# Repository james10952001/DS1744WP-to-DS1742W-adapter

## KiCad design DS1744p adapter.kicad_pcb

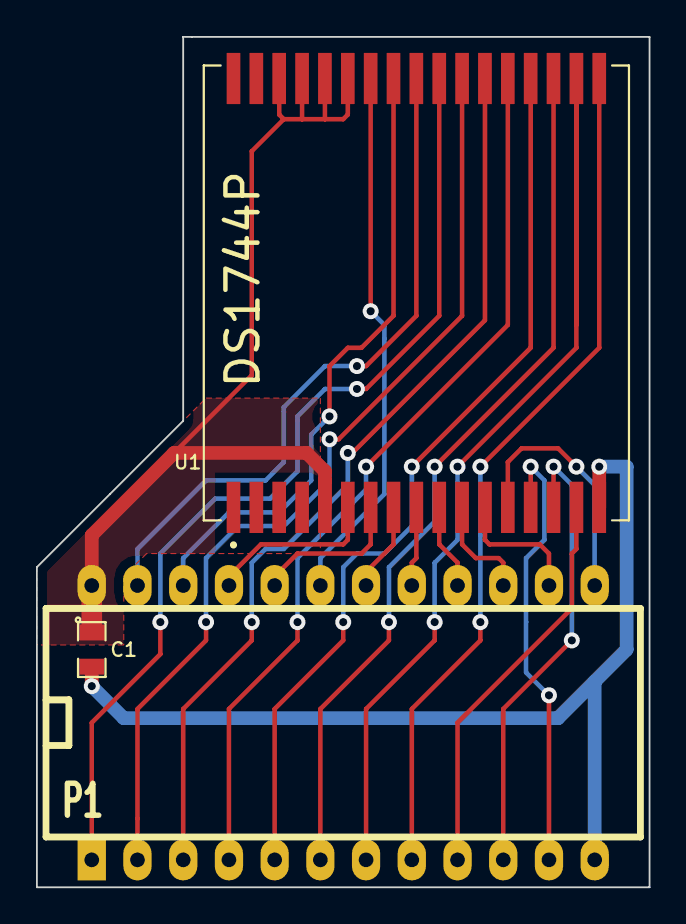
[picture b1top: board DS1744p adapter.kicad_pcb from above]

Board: 2 copper layers, 34.0 x 47.2 mm, 4 parts (1 on the bottom side), 24 nets.

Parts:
C1: 100n; SM0805
P1: DS1742W; DIP-24__600_ELL
U1: DS1744P; DALLAS_DS1554P-70+
VAL: REF; cat_300

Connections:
+3.3V: C1.1, P1.24, U1.5, U1.29, U1.30, U1.31, U1.32
/A0: P1.8, U1.18
/A1: P1.7, U1.19
/A2: P1.6, U1.20
/A3: P1.5, U1.21
/A4: P1.4, U1.22
/A5: P1.3, U1.23
/A6: P1.2, U1.24
/A7: P1.1, U1.25
/A8: P1.23, U1.26
/A9: P1.22, U1.27
/A10: P1.19, U1.28
/DQ0: P1.9, U1.16
/DQ1: P1.10, U1.15
/DQ2: P1.11, U1.14
/DQ3: P1.13, U1.13
/DQ4: P1.14, U1.12
/DQ5: P1.15, U1.11
/DQ6: P1.16, U1.10
/DQ7: P1.17, U1.9
/~CE: P1.18, U1.8
/~OE: P1.20, U1.7
/~WE: P1.21, U1.6
GND: C1.2, P1.12, U1.17

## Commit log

2019-11-02 Initial release
    Working design, verified in a Tektronix TDS3054 oscilloscope. Most of the settings can be configured through the menus but the power-on hours cannot to my knowledge. These are stored in locations 7E0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
2019-12-12 Added photo of the finished adapter

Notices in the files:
DS1744p adapter.kicad_pcb:
(c) 2019 James Sweet
